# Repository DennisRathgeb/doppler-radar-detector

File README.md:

# Doppler Radar Detector

> 24 GHz radar that measures distance (FMCW) and speed (CW Doppler), streams a live spectrum to a touchscreen UI, bridges telemetry over WiFi, and fuses the radar result with camera-based angle-of-arrival detection on a desktop application. ZHAW PM4 team project, spring 2025.

## Block Diagram

MCU-side signal flow:

Full schematic of the analog / radar board: [docs/schematic.pdf](docs/schematic.pdf).

## Highlights

- **Dual-mode 24 GHz RF front-end** — two radar modules, one CW (speed), one FMCW (distance).
- **Six-stage analog signal conditioning** (multi-feedback bandpass, ~58 dB gain at 7 kHz, I/Q channels in parallel).
- **DMA-driven dual-simultaneous ADC** feeding a **CMSIS-DSP `arm_cfft_f32`** with **ping-pong double-buffering** and SDRAM-backed FFT history — zero dropped samples under FreeRTOS.
- **TouchGFX live UI** — the FFT output buffer in SDRAM is the GUI's source buffer. No polling layer between processing and render.
- **ESP32 WiFi bridge over SPI** (STM32 master, ESP32 slave on HSPI, handshake line) → FastAPI backend.
- **YOLOv8 angle-of-arrival fusion** on the desktop — webcam + neural net → class + angle; radar → speed; Android GPS (UDP NMEA) → ground-truth reference.

## Repository Map

| Path                      | What's there |
|---------------------------|---|
| `hardware/kicad/`         | KiCad schematic + PCB (V1, V3), exported PDF, component libraries |
| `hardware/simulations/`   | LTSpice MF bandpass filter simulation |
| `hardware/calculations/`  | MATLAB: time-of-flight (`tof.m`), noise (`sigma.m`) |
| `hardware/python-tools/`  | Jupyter notebook for tolerance analysis |
| `hardware/pinout/`        | STM32 pin assignments |
| `hardware/blockdiagram/`  | Source files for the system block diagram |
| `matlab/Bodeplot/`        | Frequency-response analysis of the filter chain |
| `matlab/CW_Doppler/`      | Reference signal-chain simulation (synthetic target → FFT → peak) |
| `firmware/stm32/`         | STM32F429 firmware — Core, Drivers, Middlewares, TouchGFX, user modules (`measurement.c`, `vco.c`, `timing.c`, `esp.c`, ...), STM32CubeIDE project |
| `firmware/esp32/`         | ESP-IDF project (WiFi STA + SPI slave bridge) |
| `backend/`                | FastAPI backend (early stub) |
| `desktop-app/`            | Python fusion app: YOLOv8 detection + Android GPS UDP listener + cv2 live overlay |
| `tests/hw-concept-tolerance/` | HW tolerance scripts |
| `docs/`                   | Concept report (PDF), block diagram, amplifier-stage test notes |

## Quickstart

### STM32 firmware

Requires **STM32CubeIDE** (any recent version). Either:

- Import the `STM32CubeIDE/` folder as an existing Eclipse project, or
- Open `firmware/stm32/Radar_v2.ioc` with STM32CubeMX and regenerate the project.

Build and flash to an **STM32F429 Discovery** board. Serial log on UART1.

### ESP32 firmware

Requires **ESP-IDF** (v5.x recommended). From `firmware/esp32/`:

```bash
idf.py set-target esp32
idf.py build
idf.py -p /dev/ttyUSB0 flash monitor
```

Before flashing, edit `main/wifi.c` and replace the placeholder `WIFI_SSID` / `WIFI_PASS` with your network credentials.

### FastAPI backend

```bash
cd backend
python3 -m venv .venv && source .venv/bin/activate
pip install -r requirements.txt
uvicorn main:app --reload
```

Note: the backend is an early scaffold.

### Desktop application

```bash
cd desktop-app
python3 -m venv .venv && source .venv/bin/activate
pip install -r requirements.txt
python collect_main.py
```

The first run auto-downloads the YOLOv8n weights (~6 MB) via `ultralytics`. For ground-truth speed reference, run an Android app that streams NMEA-0183 `$GPVTG` / `$GNVTG` sentences over UDP to port 5005 on your laptop. The app tolerates the GPS feed being absent.

## Credits

ZHAW PM4 team project, spring semester 2025. Authors: Dennis Rathgeb, Bryan Uhlmann, Benjamin Tschopp.

The original collaboration took place on ZHAW's internal GitHub instance; this public repository is a slimmed mirror.

## License

MIT — see [LICENSE](LICENSE).

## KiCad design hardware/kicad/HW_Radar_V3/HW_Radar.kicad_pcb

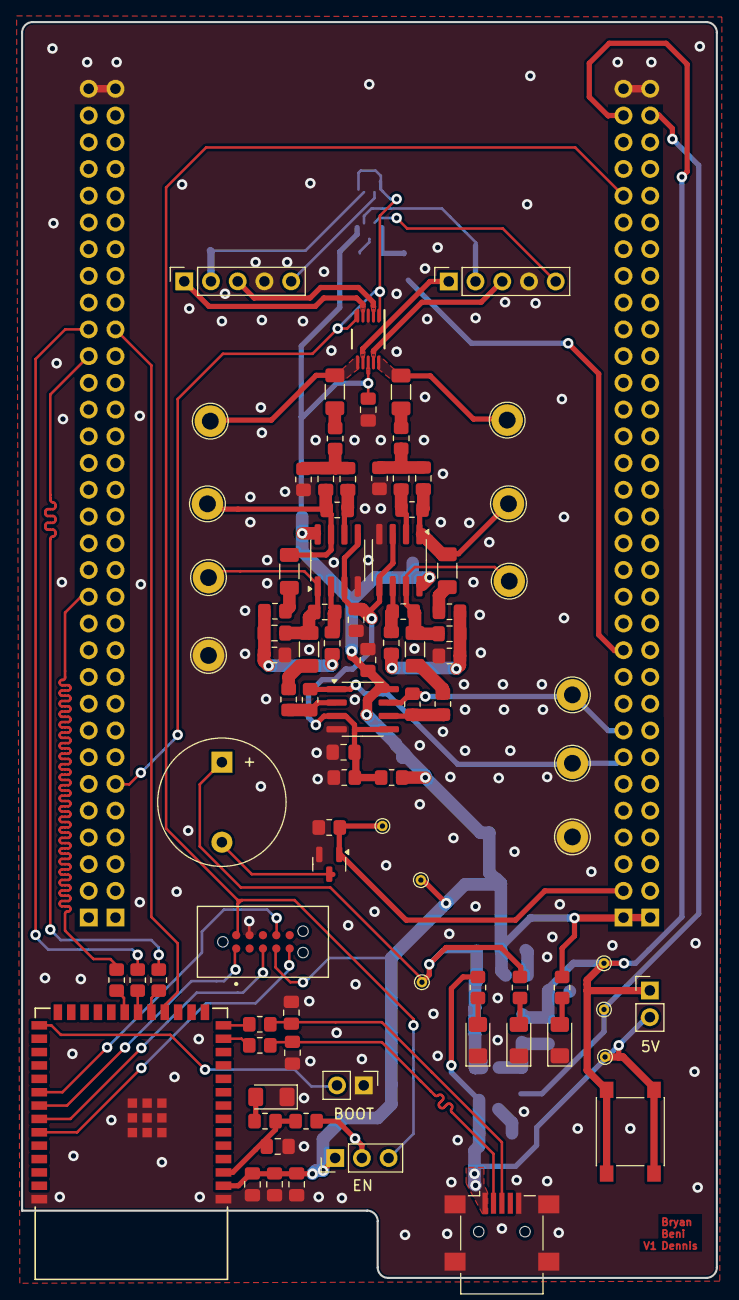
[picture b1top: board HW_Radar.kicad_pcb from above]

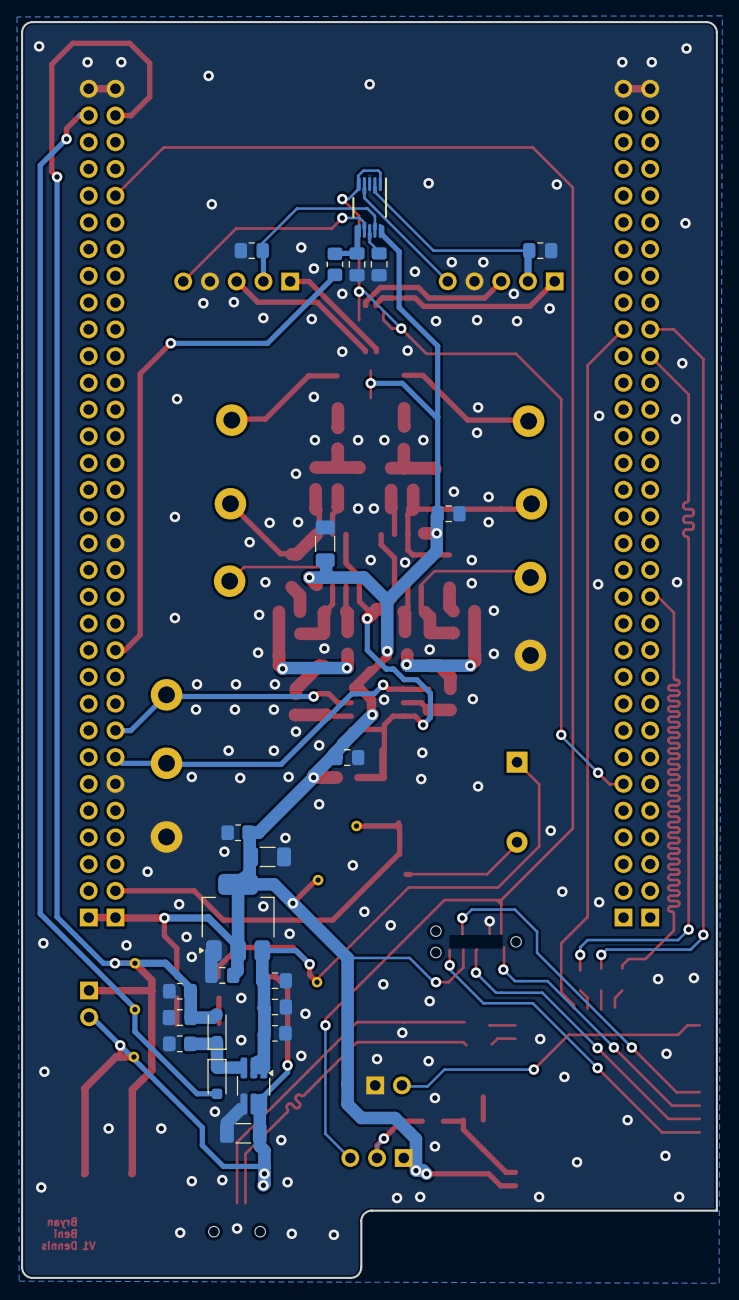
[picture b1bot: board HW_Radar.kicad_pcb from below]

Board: 2 copper layers, 66.0 x 119.3 mm, 115 parts (27 on the bottom side), 68 nets.

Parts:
1, 2, 3, 4, 6, 7, 8, 9, 10: TestPoint_Loop_D2.60mm_Drill1.6mm_Beaded
5: Q_Amplifer; TestPoint_Loop_D2.60mm_Drill1.6mm_Beaded
11, 12: 5V; TestPoint_THTPad_D1.0mm_Drill0.5mm
13: Enble_5V; TestPoint_THTPad_D1.0mm_Drill0.5mm
14: 5V_1; TestPoint_THTPad_D1.0mm_Drill0.5mm
15: 3V; TestPoint_THTPad_D1.0mm_Drill0.5mm
16: Buzzer_Input; TestPoint_THTPad_D1.0mm_Drill0.5mm
BZ1: Buzzer; Buzzer_12x9.5RM7.6
C1, C2, C5, C8, C9, C12, C15, C16, C24: 100uF; C_1206_3216Metric_Pad1.33x1.80mm_HandSolder
C3, C6, C10, C13: 15p; C_0805_2012Metric_Pad1.18x1.45mm_HandSolder
C4, C7, C11, C14: 680p; C_0805_2012Metric_Pad1.18x1.45mm_HandSolder
C17, C23, C25, C30, C32: 10uF; C_0805_2012Metric_Pad1.18x1.45mm_HandSolder
C18, C19, C20, C21, C22, C26, C29, C31, C33, C34, C35, C36, C37: 100nF; C_0805_2012Metric_Pad1.18x1.45mm_HandSolder
C27, C28: TBD; C_0805_2012Metric_Pad1.18x1.45mm_HandSolder
J1: USB_B_Mini; USB_Mini-B_Lumberg_2486_01_Horizontal
J2, J5: Conn_01x02_Pin; PinHeader_1x02_P2.54mm_Vertical
J3: Conn_01x03_Pin; PinHeader_1x03_P2.54mm_Vertical
J6: TC2050-IDC-NL; TAG-CONNECT_TC2050-IDC-NL
LED1, LED2, LED3, LED4: LEDgreen; LED_1206_3216Metric_Pad1.42x1.75mm_HandSolder
P1, P2, P3, P4: type="R" model="Conn_01x32_Female" lib=""; PinSocket_1x32_P2.54mm_Vertical
Q1: BSS316N; SOT-23
R1, R4, R9, R12: 5.6k; R_0805_2012Metric_Pad1.20x1.40mm_HandSolder
R2, R5, R10, R13: 33k; R_0805_2012Metric_Pad1.20x1.40mm_HandSolder
R3, R6, R11, R14: 56k; R_0805_2012Metric_Pad1.20x1.40mm_HandSolder
R7, R15: 1k; R_0805_2012Metric_Pad1.20x1.40mm_HandSolder
R8, R16: 8.2k; R_0805_2012Metric_Pad1.20x1.40mm_HandSolder
R17, R20, R22, R23, R26: 100k; R_0805_2012Metric_Pad1.20x1.40mm_HandSolder
R18, R19, R28: 680; R_0805_2012Metric_Pad1.20x1.40mm_HandSolder
R21: 220; R_0805_2012Metric_Pad1.20x1.40mm_HandSolder
R24, R25, R27: 10k; R_0805_2012Metric_Pad1.20x1.40mm_HandSolder
R29, R30, R31, R32, R33: 0; R_0805_2012Metric_Pad1.20x1.40mm_HandSolder
R34: 180; R_0805_2012Metric_Pad1.20x1.40mm_HandSolder
SD1, SD2: SD103AWS; D_SOD-323_HandSoldering
SW1: type="R" model="SW_Push" lib=""; SW_SPST_PTS645
U1, U2, U3: MCP6002-xSN; SOIC-8_3.9x4.9mm_P1.27mm
U4: SiP32508; TSOT-23-6_HandSoldering
U5: LD1117S33TR_SOT223; SOT-223-3_TabPin2
U6: ESP32-S3-WROOM-1-N4R8; ESP32-S3-WROOM-1_EXP
U7, U8: TS5A23159DGSR; DGS0010A_N
Y1, Y2: Radar K-LC5-RFB-00C; Radar_K-LC5

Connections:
+3V0: 15.1, C1.1, C19.2, C20.2, C22.2, C23.1, C24.1, C29.1, C30.2, C32.2, C34.2, C35.2, J3.1, J6.4, P3.1, P4.1, R21.1, R23.1, R24.2, U1.8 (V+), U2.8 (V+), U3.8 (V+), U5.2 (VO), U6.2 (3V3), U7.8 (V+), U8.8 (V+), U8.10 (COM1)
+5V: 11.1, C16.1, J1.1 (VBUS), J2.2, R18.1, SW1.1, U4.5 (IN), U4.6 (IN)
Amplifier_Offset: C25.1, C26.1, R24.1, R25.2, U1.3 (+), U1.5 (+), U2.3 (+), U2.5 (+), U3.3 (+), U3.5 (+)
Buzzer: 16.1, P3.2, Q1.1 (G), R26.1
DAC_OUT2: P3.11, R34.1
ESP_EN: J3.3, J6.10, P3.28
ESP_MISO: P1.13, R33.1
ESP_MOSI: P1.22, R31.1
ESP_SCK: P1.23, R32.1
ESP_SS: P2.23, U6.18 (IO10)
ESP_TCK: J6.7, U6.32 (IO39)
ESP_TDI: J6.3, U6.34 (IO41)
ESP_TDO: J6.1, U6.33 (IO40)
ESP_TMS: J6.5, U6.35 (IO42)
GND: 1.1, 2.1, C1.2, C16.2, C17.2, C18.2, C19.1, C20.1, C21.2, C22.1, C23.2, C24.2, C25.2, C26.2, C27.1, C28.1, C29.2, C30.1, C31.1, C32.1, C33.2, C34.1, C35.1, C36.2, C37.2, J1.5 (GND), J1.6 (Shield), J5.1, J6.9, LED1.1 (K), LED2.1 (K), LED3.1 (K), LED4.1 (K), P1.32, P2.32, P3.6, P3.15, P3.32, P4.32, Q1.2 (S), R2.1, R5.1, R10.1, R13.1, R17.2, R20.2, R22.2, R23.2, R25.1, R26.2, U1.4 (V-), U2.4 (V-), U3.4 (V-), U4.4 (GND), U5.1 (GND), U6.1 (GND), U6.40 (GND), U6.41 (GND), U6.42, U6.43, U6.44, U6.45, U6.46 (GND), U6.47 (GND), U6.48 (GND), U6.49 (GND), U7.3 (GND), U8.3 (GND), Y1.4 (GND), Y2.4 (GND)
Input_Enable_5V: 13.1, P4.31, SD2.2 (A)
unnamed: BZ1.2 (-), Q1.3 (D)
unnamed: C2.2, R1.1
unnamed: C3.1, C4.1, R1.2, R2.2
unnamed: 7.1, C3.2, C5.1, R3.2, U1.7
unnamed: C5.2, R4.1
unnamed: C6.1, C7.1, R4.2, R5.2
unnamed: 8.1, C6.2, C8.1, R6.2, U1.1
unnamed: C8.2, R7.1
unnamed: C9.2, R9.1
unnamed: C10.1, C11.1, R9.2, R10.2
unnamed: 9.1, C10.2, C12.1, R11.2, U2.1
unnamed: C12.2, R12.1
unnamed: C13.1, C14.1, R12.2, R13.2
unnamed: 10.1, C13.2, C15.1, R14.2, U2.7
unnamed: C15.2, R15.1
unnamed: J3.2, R27.1
unnamed: J5.2, U6.27 (IO0)
unnamed: LED1.2 (A), R18.2
unnamed: LED2.2 (A), R19.2
unnamed: LED3.2 (A), R21.2
unnamed: LED4.2 (A), R28.2
unnamed: R20.1, SD1.1 (K), SD2.1 (K), U4.3 (EN)
unnamed: C7.2, R6.1, U1.2 (-)
unnamed: C4.2, R3.1, U1.6 (-)
unnamed: C11.2, R11.1, U2.2 (-)
unnamed: C14.2, R14.1, U2.6 (-)
unnamed: R7.2, R8.1, U3.2 (-)
unnamed: R15.2, R16.1, U3.6 (-)
unnamed: C31.2, R27.2, R28.1, U6.3 (EN)
unnamed: R31.2, U6.19 (IO11)
unnamed: R32.2, U6.20 (IO12)
unnamed: R33.2, U6.21 (IO13)
unnamed: R29.2, U6.13 (IO19)
unnamed: R30.2, U6.14 (IO20)
unnamed: C33.1, R34.2, U8.6 (COM2)
unnamed: C37.1, U8.9 (NC1), Y1.2 (VCC)
unnamed: U8.7 (NC2), Y1.5 (VCO_in)
unnamed: C36.1, U8.2 (NO1), Y2.2 (VCC)
unnamed: U8.4 (NO2), Y2.5 (VCO_in)
OUT_I: 6.1, P3.8, R16.2, U3.7
OUT_Q: 5.1, P3.7, R8.2, U3.1
Output_Enable_5V: 12.1, C17.1, J2.1, P3.31, R17.1, SD1.2 (A), SW1.2
RADAR_I_1: U7.9 (NC1), Y1.3 (IF_I)
RADAR_I_2: U7.2 (NO1), Y2.3 (IF_I)
RADAR_OUT_I: 4.1, C9.1, U7.10 (COM1)
RADAR_OUT_Q: 3.1, C2.1, U7.6 (COM2)
RADAR_Q_1: U7.7 (NC2), Y1.1 (IF_Q)
RADAR_Q_2: U7.4 (NO2), Y2.1 (IF_Q)
SIG_SEL: P2.6, U7.1 (IN1), U7.5 (IN2), U8.1 (IN1), U8.5 (IN2)
USB_D+: C28.2, J1.3 (D+), R30.1
USB_D-: C27.2, J1.2 (D-), R29.1
V5_1: 14.1, BZ1.1 (+), C18.1, C21.1, R19.1, R22.1, U4.1 (OUT), U4.2 (OUT), U5.3 (VI)

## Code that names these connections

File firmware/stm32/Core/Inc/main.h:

/* USER CODE BEGIN Header */
/**
  ******************************************************************************
  * @file           : main.h
  * @brief          : Header for main.c file.
  *                   This file contains the common defines of the application.
  ******************************************************************************
  * @attention
  *
  * <h2><center>&copy; Copyright (c) 2020 STMicroelectronics.
  * All rights reserved.</center></h2>
  *
  * This software component is licensed by ST under Ultimate Liberty license
  * SLA0044, the "License"; You may not use this file except in compliance with
  * the License. You may obtain a copy of the License at:
  *                             www.st.com/SLA0044
  *
  ******************************************************************************
  */
/* USER CODE END Header */

/* Define to prevent recursive inclusion -------------------------------------*/
#ifndef __MAIN_H
#define __MAIN_H

#ifdef __cplusplus
extern "C" {
#endif

/* Includes ------------------------------------------------------------------*/
#include "stm32f4xx_hal.h"

/* Private includes ----------------------------------------------------------*/
/* USER CODE BEGIN Includes */

/* USER CODE END Includes */

/* Exported types ------------------------------------------------------------*/
/* USER CODE BEGIN ET */

/* USER CODE END ET */

/* Exported constants --------------------------------------------------------*/
/* USER CODE BEGIN EC */

/* USER CODE END EC */

/* Exported macro ------------------------------------------------------------*/
/* USER CODE BEGIN EM */

/* USER CODE END EM */

void HAL_TIM_MspPostInit(TIM_HandleTypeDef *htim);

/* Exported functions prototypes ---------------------------------------------*/
void Error_Handler(void);

/* USER CODE BEGIN EFP */

/* USER CODE END EFP */

/* Private defines -----------------------------------------------------------*/
#define VSYNC_FREQ_Pin GPIO_PIN_2
#define VSYNC_FREQ_GPIO_Port GPIOE
#define RENDER_TIME_Pin GPIO_PIN_3
#define RENDER_TIME_GPIO_Port GPIOE
#define FRAME_RATE_Pin GPIO_PIN_4
#define FRAME_RATE_GPIO_Port GPIOE
#define MCU_ACTIVE_Pin GPIO_PIN_5
#define MCU_ACTIVE_GPIO_Port GPIOE
#define SIG_SEL_Pin GPIO_PIN_13
#define SIG_SEL_GPIO_Port GPIOC
#define BUZZER_Pin GPIO_PIN_6
#define BUZZER_GPIO_Port GPIOF
#define SIGNAL_Q_Pin GPIO_PIN_1
#define SIGNAL_Q_GPIO_Port GPIOC
#define SIGNAL_I_Pin GPIO_PIN_3
#define SIGNAL_I_GPIO_Port GPIOC
#define VCO_Pin GPIO_PIN_5
#define VCO_GPIO_Port GPIOA
#define ESP_EN_Pin GPIO_PIN_11
#define ESP_EN_GPIO_Port GPIOD
#define EN_PCB_OUT_Pin GPIO_PIN_2
#define EN_PCB_OUT_GPIO_Port GPIOG
#define EN_PCB_IN_Pin GPIO_PIN_3
#define EN_PCB_IN_GPIO_Port GPIOG

/* USER CODE BEGIN Private defines */

/* USER CODE END Private defines */

#ifdef __cplusplus
}
#endif

#endif /* __MAIN_H */

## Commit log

2026-04-18 Initial commit: ZHAW PM4 Doppler radar detector
    Team project: CW Doppler radar with STM32F429 + ESP32, analog
    signal conditioning, DMA-driven acquisition, CMSIS-DSP FFT + CFAR,
    TouchGFX live UI, FastAPI backend, YOLOv8 angle-of-arrival sensor
    fusion desktop app.
2026-04-18 Add schematic PDF, higher-quality block diagram, MCU data-path figure
    - docs/schematic.pdf: KiCad schematic export of the custom radar board
    - docs/block-diagram.png: replaced with the detailed system-level diagram
    - docs/mcu-data-path.png: signal-flow figure showing Dual-ADC → DMA →
    SRAM → FFT plus the DAC/VCO transmit branch
    - README.md: reference the new figures and schematic
2026-04-18 Clean up README: drop folder-map section, soften mirror description
2026-04-18 Remove SUMMARY.md (kept in author's private notes)
